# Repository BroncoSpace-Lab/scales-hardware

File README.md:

# scales-hardware
Hardware design files for the Spacecraft Compartmentalized Autonomous Learning and Edge Computing System (SCALES)

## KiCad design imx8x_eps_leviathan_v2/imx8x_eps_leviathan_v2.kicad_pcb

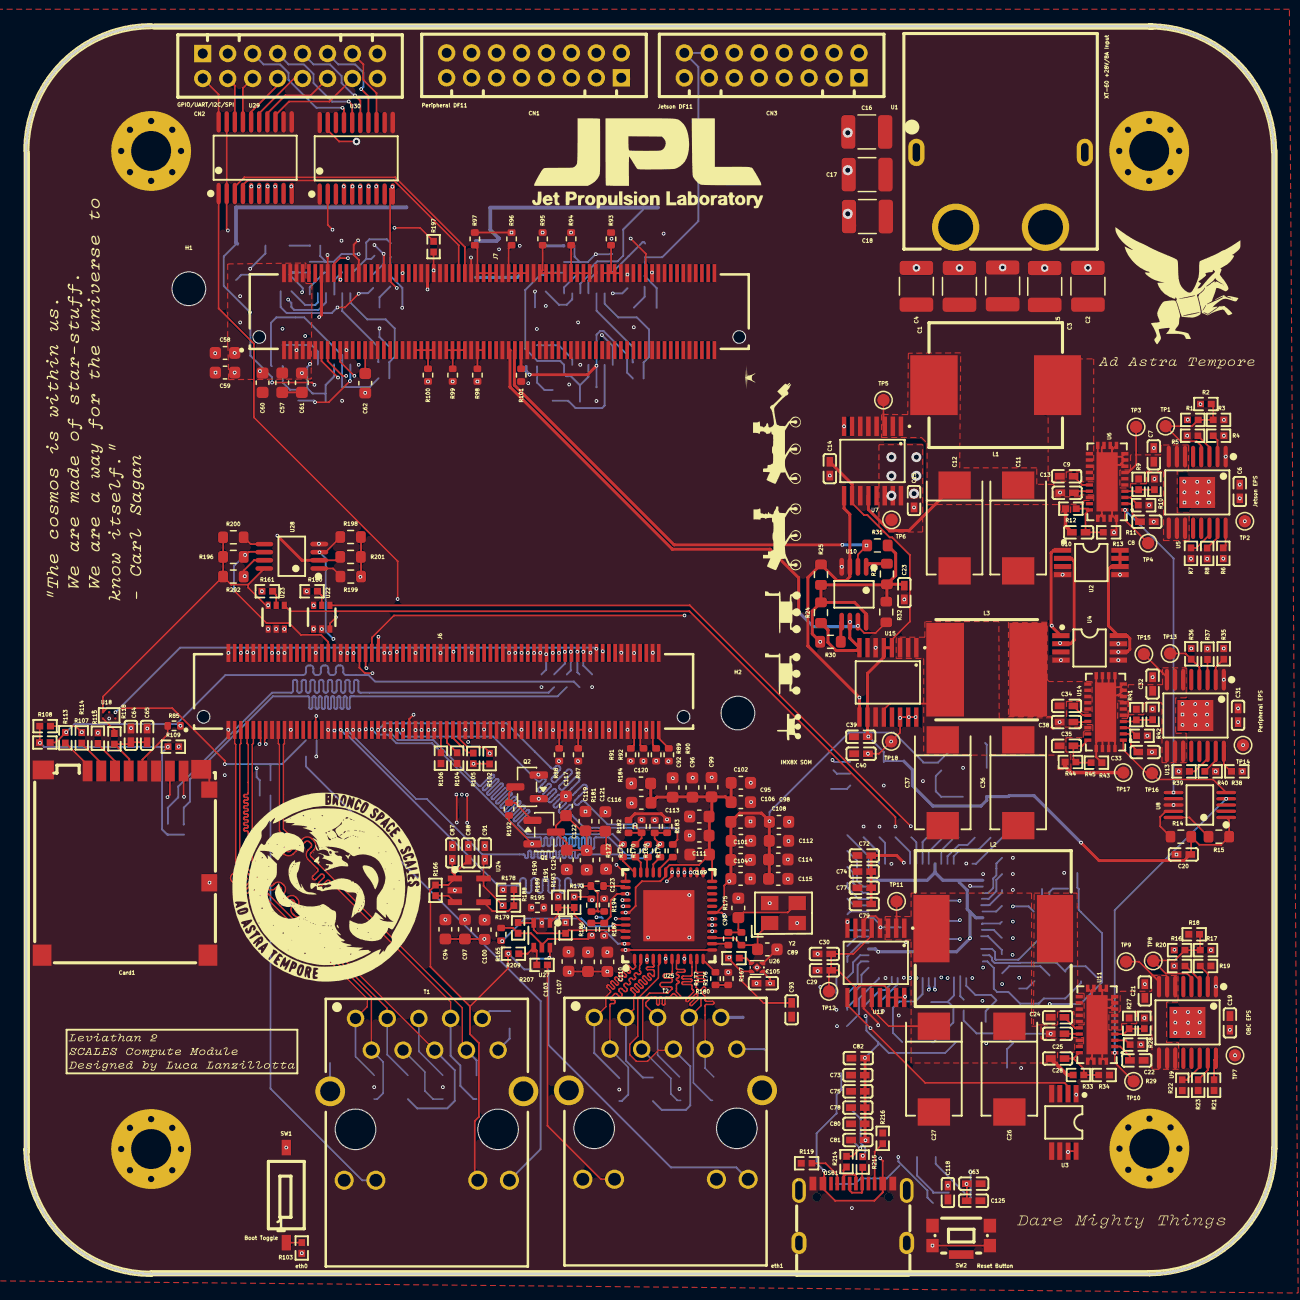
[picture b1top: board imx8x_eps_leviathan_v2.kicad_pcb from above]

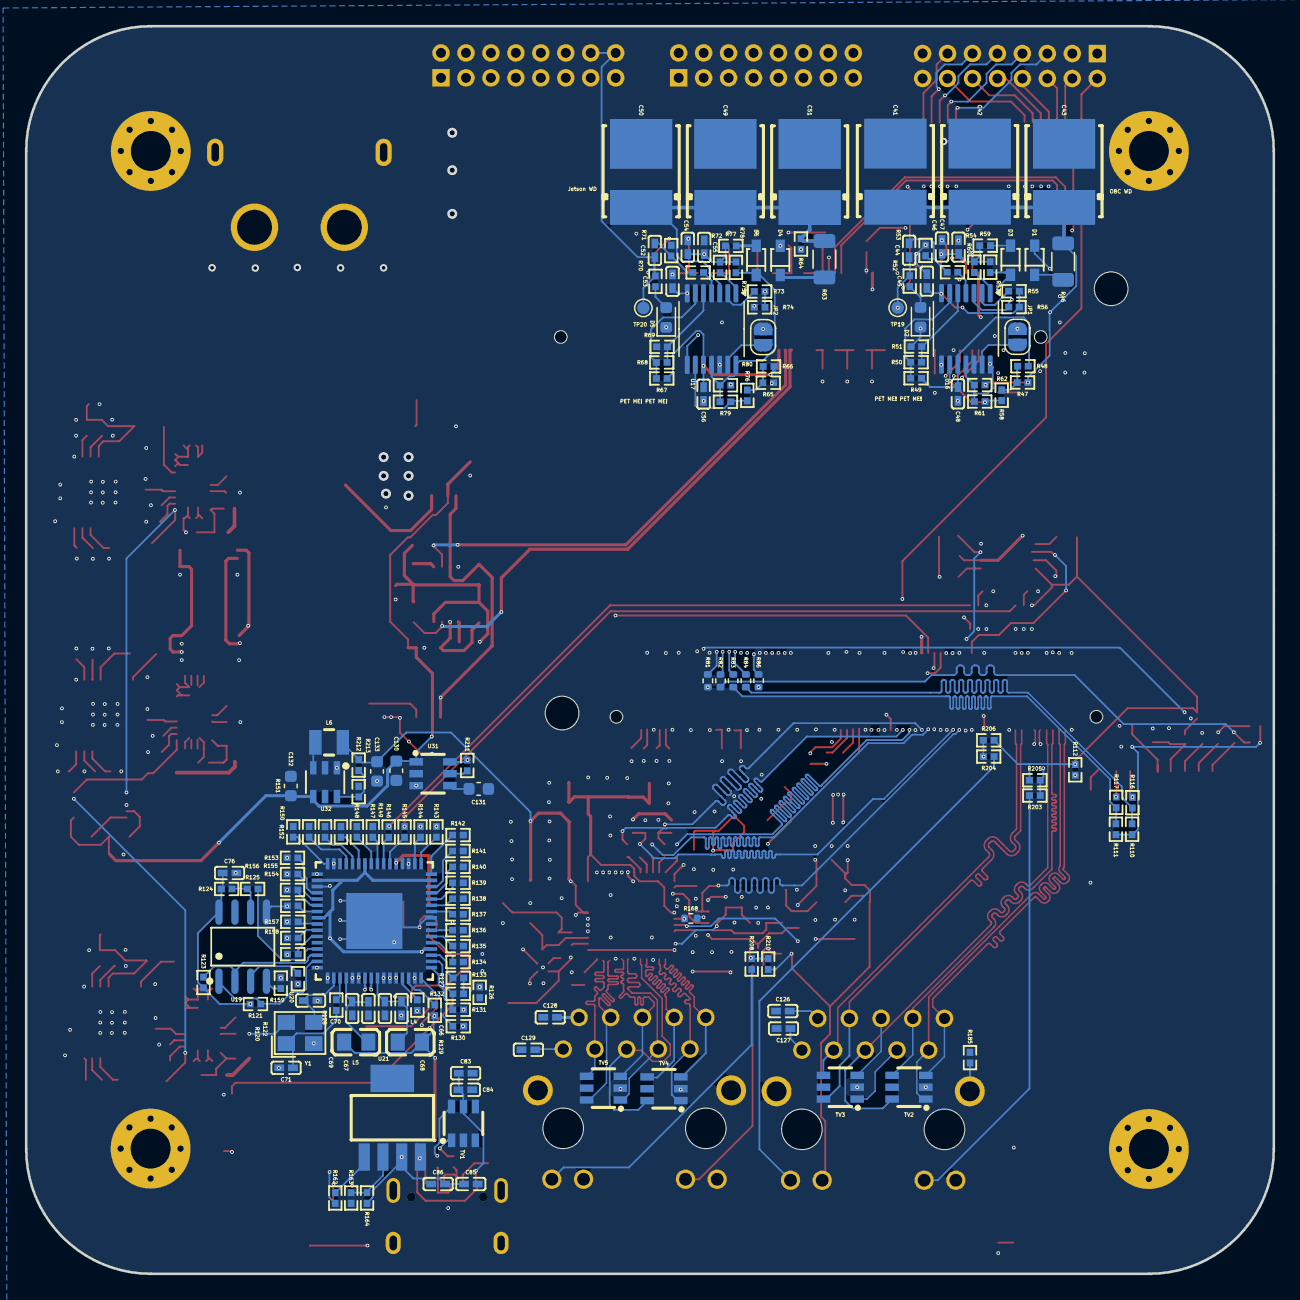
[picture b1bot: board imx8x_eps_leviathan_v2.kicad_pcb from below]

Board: 6 copper layers, 100.0 x 100.0 mm, 441 parts (160 on the bottom side), 317 nets.

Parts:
C1, C2, C3, C4, C5, C16, C17, C18: 10u; C_1210_3225Metric
C6, C19, C31: 220n; C0402
C7, C21, C32: 22n; C0402
C8, C85: 1u; C0402
C9, C13, C14, C15, C20, C23, C24, C28, C29, C30, C34, C38, C39, C40, C63, C68, C69, C74, C75, C76, C77, C78, C79, C80, C82, C84, C86, C87, C88, C91, C93, C105, C125, C126, C127, C128, C129: 100n; C0402
C10, C25, C35: 10p; C0402
C11, C12, C26, C27, C36, C37: 47u; CAP-SMD_L7.3-W4.3-FD
C22, C33: 0.47u; C0402
C41, C42, C43, C49, C50, C51: 100u; CAP-SMD_L7.3-W6.1_TCN4227M025R0100
C44, C45, C46, C47, C48, C52, C53, C54, C55, C56, C64, C65: 10u; C0402
C57, C58: 22u; C_0603_1608Metric
C59, C60, C132: 4.7u; C_0603_1608Metric
C61, C95, C96, C97, C101, C102, C103, C108, C109, C113, C119, C122: 100n; C_0603_1608Metric
C62: 220n; C_0603_1608Metric
C66, C67, C72, C73, C81: 4.7u; C0402
C70, C71: 12p; C0402
C83: 2.2u; C0402
C89, C90: 18p; C_0603_1608Metric
C92, C94, C98, C99, C100, C104, C106, C111, C112, C117, C121, C130: 1u; C_0603_1608Metric
C107, C114, C116, C123: 10n; C_0603_1608Metric
C110, C115, C120, C124, C133: 10u; C_0603_1608Metric
C118: 2.2n; C0402
C131: 47u; C_0603_1608Metric
CN1, CN2, CN3: DF11-16DP-2DSA; CONN-TH_DF11-16DP-2DSA-08
Card1: 5027740891; TF-SMD_5027740891
D1, D3, D4, D6: 1N4448WS-7-F; SOD-323_L1.8-W1.3-LS2.5-RD
D2, D5: GREEN; LED_0603_1608Metric
H1, H2: MountingHole; MountingHole_2.7mm_M2.5
J1, J2, J3, J4: Conn_01x01_Socket; MountingHole_3.2mm_M3_Pad_Via
J6, J7: BTH-070-02-L-D-A; SAMTEC_BTH-070-02-L-D-A
JP1, JP2: SolderJumper_2_Open; SolderJumper-2_P1.3mm_Open_RoundedPad1.0x1.5mm
L1: 35u; IND-SMD_L10.7-W10.0_ETQP5MXXXX
L2: 6.1u; IND-SMD_FTKB1207-6R1NT
L3: 10u; IND-SMD_L8.0-W8.0
L4, L5: 600R/1000MHz; L0805
L6: 2.2u; IND-SMD_L2.5-W2.0_YXMBL252010P
Q1: IRLML6401; SOT-23
Q2: BSS138; SOT-23
R1, R2, R4, R16, R19, R35, R36, R55, R57, R73, R75, R102, R103, R104, R105, R106, R129, R159, R211: 1k; R0402
R3, R5, R6, R7, R8, R20, R21, R22, R23, R37, R38, R39, R40: 15k; R0402
R9, R27, R41: 47k; R0402
R10, R28, R42, R125, R197: 2k; R0402
R11, R29, R43: 110k; R0402
R12: 196k; R0402
R13, R18, R47, R48, R49, R50, R53, R54, R65, R66, R67, R68, R71, R72, R120, R121, R123, R124, R127, R132, R133, R134, R135, R136, R137, R138, R139, R140, R141, R142, R143, R144, R147, R148, R149, R150, R151, R152, R153, R154, R155, R156, R157, R158, R160, R161, R162, R163, R166, R180, R188, R205, R206, R209, R210: 10k; R0402
R14: 14k; R_0603_1608Metric
R15: 17k; R_0603_1608Metric
R17: 56.2k; R0402
R24, R25, R26, R30, R31, R32: 4.7k; R_0603_1608Metric
R33: 240k; R0402
R34, R56, R58, R59, R61, R62, R64, R74, R76, R77, R79, R80, R213: 100k; R0402
R44: 20.8k; R0402
R45: 5k; R0402
R46, R63: 10; R_1206_3216Metric
R51, R52, R69, R70: 3k; R0402
R60, R78: 4.7M; R0402
R81, R82, R83, R84, R85, R86, R169, R170, R171, R172, R173: 22; R_0402_1005Metric
R87, R88, R89, R90, R91, R92, R93, R94, R95, R96, R97, R98, R99, R100, R101, R177, R181, R192, R195: 10k; R_0402_1005Metric
R107, R108, R109, R110, R111, R112: 49.9k; R0402
R113, R114, R115, R116, R117, R130, R131, R145, R146: 22; R0402
R118, R122: 0; R0402
R119, R216: 5.1k; R0402
R126: 12k; R0402
R128, R203, R204, R207, R208: 200; R0402
R164: 16.5k; R0402
R165: 2k; R_0402_1005Metric
R167: 1M; R_0402_1005Metric
R168: 15k; R_0402_1005Metric
R174: 0; R_0402_1005Metric
R175: 100; R_0402_1005Metric
R176: 1k; R_0402_1005Metric
R178: 2.55k; R0402
R179: 13k; R0402
R182, R183, R184, R187, R194: 2.49k; R_0402_1005Metric
R185: 1M; R0402
R186, R193: 5.76k; R_0402_1005Metric
R189, R191: 2.49k; R0402
R190: 5.76k; R0402
R196, R198, R199, R200, R201, R202: 10k; R_0603_1608Metric
R212: 200k; R0402
R214, R215: 27; R0402
SW1: SW_DIP_x01; SW-SMD_1.27-1P-TPPT
SW2: KMR221GLFS; KEY-SMD_KMR2XXGXXX
T1, T2: WE-RJ45_7499111121A; 7499111121A
TP1, TP2, TP3, TP4, TP5, TP6, TP7, TP8, TP9, TP10, TP11, TP12, TP13, TP14, TP15, TP16, TP17, TP18, TP19, TP20: TestPoint; TestPoint_Pad_D1.0mm
TV1, TV2, TV3, TV4, TV5: SRV05-4.TCT; SOT-23-6_L2.9-W1.6-P0.95-LS2.8-BR
U1: XT60PW-F_C428722; TH_2P-XT60PW-F
U2, U3, U4: MCP9808T-E/MS; MSOP-8_L3.0-W3.0-P0.65-LS4.9-BL
U5, U9, U13: TPS1HB08BQPWPRQ1; HTSSOP-16_L5.0-W4.4-P0.65-LS6.4-TL-EP2.9
U6, U11, U14: LT8612EUDE#PBF; QFN-28_L6.0-W3.0-P0.50-BL-EP
U7, U12, U15: INA260AIPWR; TSSOP-16_L5.0-W4.4-P0.65-LS6.4-BL-1
U8: LTC6902; MSOP-10_L3.0-W3.0-P0.50-LS5.0-BL
U10, U28: TCA4307DGKR; VSSOP-8_L3.0-W3.0-P0.65-LS4.9-BL
U16, U17: TLV1704; TSSOP-14_4.4x5mm_P0.65mm
U18: BD2204GUL-E2; BGA-6_L1.5-W1.0-P0.50_BD2204GUL-E2
U19: CAT93C66VI-GT3; SOIC-8_L4.9-W3.9-P1.27-LS6.0-BL
U20: FT2232HL; QFN-64_L9.0-W9.0-P0.50-TL-EP4.3
U21: LP38693MP-ADJ/NOPB; SOT-223-5_L6.5-W3.5-P1.50-LS7.0-BL
U22, U23: TXS0101DCKR; SC-70-6_L2.0-W1.3-P0.65-LS2.1-BR
U24: MCP1824T-ADJE/OT; SOT-23-5_L3.0-W1.7-P0.95-LS2.8-BL
U25: DP83867CRRGZR; VQFN-48_L7.0-W7.0-P0.50-BL-EP4.1
U26: TLV71310PDQNR; X2SON-4_L1.0-W1.0-P0.65-TL-EP
U27: 74LVC2G07GW; SOT-363_L2.1-W1.3-P0.65-LS2.2-BL
U29, U30: TXS0108EPWR; TSSOP-20_L6.5-W4.4-P0.65-LS6.4-BL
U31: TPS22917DBVR; SOT-23-6_L2.9-W1.6-P0.95-LS2.8-BR
U32: TLV62569PDDCR; SOT-23-6_L2.9-W1.6-P0.95-LS2.8-BL
USB1: TYPE-C 16PIN 2MD; USB-C-SMD_TYPE-C-6PIN-2MD-073
Y1: Crystal_GND24; CRYSTAL-SMD_4P-L3.2-W2.5-BL
Y2: 25MHz; CRYSTAL-SMD_4P-L3.2-W2.5-BL-2

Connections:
1V8_FTDI: C72.2, C74.2, C77.2, C79.2, U20.12 (VCORE), U20.37 (VCORE), U20.49 (VREGOUT), U20.64 (VCORE)
3V3_FTDI: C73.2, C75.2, C76.2, C78.2, C80.2, C81.2, C82.2, C85.2, C86.2, L4.1, L5.1, R121.2, R123.2, R124.2, R129.2, R159.1, R164.1, U19.8 (VCC), U20.20 (VCCIO), U20.31 (VCCIO), U20.42 (VCCIO), U20.50 (VREGIN), U20.56 (VCCIO), U21.3 (OUT)
+1.8V_OBC_Perif: C93.1, C95.1, C98.1, C101.1, C104.1, C108.1, C112.1, C114.1, C115.1, C133.1, L6.2, Q1.2 (S), R165.2, R180.1, R181.1, R183.1, R186.1, R188.1, R190.1, R192.1, R193.1, R212.1, U25.19 (VDDIO), U25.30 (VDDIO), U25.41 (VDDIO), U26.4 (IN), U27.5 (VCC)
+3.3V_OBC: C14.1, C20.1, C29.1, C30.1, C39.1, C57.1, C58.1, C59.1, C60.1, C61.1, C130.1, C132.1, D1.2 (A), J7.132 (D66), J7.133 (C67), J7.134 (D67), J7.135 (C68), J7.136 (D68), J7.137 (C69), J7.138 (D69), J7.139 (C70), J7.140 (D70), R14.1, R15.1, R120.2, R197.1, TP12.1 (1_1), U2.6 (A1), U2.7 (A0), U2.8 (VDD), U3.7 (A0), U3.8 (VDD), U4.6 (A1), U4.8 (VDD), U7.10 (VS), U8.1 (V+), U12.5 (A0), U12.10 (VS), U12.14 (IN-), U15.4 (A1), U15.5 (A0), U15.10 (VS), U29.2 (VCCA), U29.19 (VCCB), U30.2 (VCCA), U30.19 (VCCB), U31.1 (VIN), U32.4 (VIN)
+3.3V_OBC_Perif: C23.1, C63.2, C87.1, C88.1, C125.1, R24.1, R25.1, R26.1, R30.1, R31.1, R32.1, R112.2, R166.1, R196.1, R198.1, R199.1, R200.1, R201.1, R202.1, R205.1, R206.1, R209.1, R210.1, R211.1, T1.11, T1.13, T2.11, T2.13, U10.8 (VCC), U18.A1 (VIN1), U22.6 (VCCB), U23.6 (VCCB), U24.1 (VIN), U28.8 (VCC), U31.6 (VOUT)
+5V_Perif: C40.1, CN1.1, CN1.2, CN1.3, CN1.4, CN1.5, CN1.6, CN1.7, CN1.8, TP18.1 (1_1), U15.14 (IN-)
+20V_Jetson: C15.1, C16.1, C17.1, C18.1, CN3.1, CN3.2, CN3.3, CN3.4, CN3.5, CN3.6, CN3.7, CN3.8, D4.2 (A), TP6.1 (1_1), U7.14 (IN-)
+V_Batt: C1.1, C2.1, C3.1, C4.1, C5.1, C6.1, C19.1, C31.1, R17.2, TP2.1 (1_1), TP7.1 (1_1), TP14.1 (1_1), U1.3 (+), U5.17 (VBB), U9.17 (VBB), U13.17 (VBB)
/IMX8XQXP SCALES Mariner Carrier Board/Debug USB - UART/DEBUG_USB_DN: R214.2, TV1.1, U20.7 (DM)
/IMX8XQXP SCALES Mariner Carrier Board/Debug USB - UART/DEBUG_USB_DP: R215.2, TV1.6, U20.8 (DP)
/IMX8XQXP SCALES Mariner Carrier Board/Debug USB - UART/FTDI_OSCI: C70.1, U20.2 (OSCI), Y1.3
/IMX8XQXP SCALES Mariner Carrier Board/Debug USB - UART/FTDI_OSCO: C71.1, R128.2, Y1.1
/IMX8XQXP SCALES Mariner Carrier Board/Debug USB - UART/M40_UART0_RX: R145.1, U23.4 (B)
/IMX8XQXP SCALES Mariner Carrier Board/Debug USB - UART/M40_UART0_TX: R146.1, U22.4 (B)
/SCALES_EPS/Jetson_Subsystem/WD_Jetson/WDT-VIN: R64.2, R65.2, R74.1, R80.1
/SCALES_EPS/Jetson_Subsystem/WD_Jetson/WDT-VP: R68.1, R69.2, U17.5 (+)
/SCALES_EPS/OBC_Subsystem/WD_OBC/WDT-VIN: C41.1, C42.1, C43.1, R46.2, R47.2, R56.1, R62.1, U16.3 (V+)
/SCALES_EPS/OBC_Subsystem/WD_OBC/WDT-VP: R50.1, R51.2, U16.5 (+)
ETH1_A_TX_N: T2.2 (D1-), TV4.1, U25.2 (TD_M_A)
ETH1_A_TX_P: T2.1 (D1+), TV4.3, U25.1 (TD_P_A)
ETH1_B_TX_N: T2.6 (D2-), TV4.6, U25.5 (TD_M_B)
ETH1_B_TX_P: T2.3 (D2+), TV4.4, U25.4 (TD_P_B)
ETH1_C_TXCLK_N: T2.5 (D3-), TV5.3, U25.8 (TD_M_C)
ETH1_C_TXCLK_P: T2.4 (D3+), TV5.1, U25.7 (TD_P_C)
ETH1_D_RXDV_N: T2.8 (D4-), TV5.4, U25.11 (TD_M_D)
ETH1_D_RXDV_P: T2.7 (D4+), TV5.6, U25.10 (TD_P_D)
ETH1_LED0: R208.2, R210.2, U27.6 (1Y)
ETH1_LED2: R207.2, R209.2, U27.4 (2Y)
GND: C1.2, C2.2, C3.2, C4.2, C5.2, C6.2, C7.2, C8.2, C11.2, C12.2, C13.2, C14.2, C15.2, C16.2, C17.2, C18.2, C19.2, C20.2, C21.2, C22.2, C23.2, C26.2, C27.2, C28.2, C29.2, C30.2, C31.2, C32.2, C33.2, C36.2, C37.2, C38.2, C39.2, C40.2, C41.2, C42.2, C43.2, C45.1, C46.1, C47.1, C48.1, C49.2, C50.2, C51.2, C53.1, C54.1, C55.1, C56.1, C57.2, C58.2, C59.2, C60.2, C61.2, C62.2, C63.1, C64.1, C65.1, C66.1, C67.1, C68.1, C69.1, C70.2, C71.2, C72.1, C73.1, C74.1, C75.1, C76.1, C77.1, C78.1, C79.1, C80.1, C81.1, C82.1, C83.1, C84.1, C85.1, C86.1, C87.2, C88.2, C89.1, C90.1, C91.2, C92.2, C93.2, C94.2, C95.2, C96.2, C97.2, C98.2, C99.2, C100.2, C101.2, C102.2, C103.2, C104.2, C105.2, C106.2, C107.2, C108.2, C109.2, C110.2, C111.2, C112.2, C113.2, C114.2, C115.2, C116.2, C117.2, C118.2, C119.2, C120.2, C121.2, C122.2, C123.2, C124.2, C125.2, C126.2, C127.2, C128.2, C129.2, C130.2, C131.2, C132.2, C133.2, CN1.9, CN1.10, CN1.12, CN1.14, CN1.16, CN2.15, CN2.16, CN3.9, CN3.10, CN3.11, CN3.12, CN3.13, CN3.15, Card1.6 (VSS), Card1.10 (DET), Card1.11 (SHELL), Card1.12 (SHELL), Card1.13 (SHELL), Card1.14 (SHELL), D2.1 (K), D5.1 (K), J1.1 (1_1), J2.1 (1_1), J3.1 (1_1), J4.1 (1_1), J6.03 (A2), J6.06 (B3), J6.09 (A5), J6.12 (B6), J6.13 (A7), J6.18 (B9), J6.23 (A12), J6.24 (B12), J6.30 (B15), J6.36 (B18), J6.39 (A20), J6.40 (B20), J6.46 (B23), J6.49 (A25), J6.52 (B26), J6.58 (B29), J6.61 (A31), J6.64 (B32), J6.71 (A36), J6.74 (B37), J6.79 (A40), J6.80 (B40), J6.89 (A45), J6.90 (B45), J6.100 (B50), J6.103 (A52), J6.108 (B54), J6.111 (A56), J6.120 (B60), J6.121 (A61), J6.126 (B63), J6.131 (A66), J6.139 (A70), J6.140 (B70), J7.09 (C5), J7.10 (D5), J7.19 (C10), J7.22 (D11), J7.29 (C15), J7.36 (D18), J7.39 (C20), J7.46 (D23), J7.49 (C25), J7.56 (D28), J7.59 (C30), J7.62 (D31), J7.69 (C35), J7.70 (D35), J7.79 (C40), J7.80 (D40), J7.89 (C45), J7.90 (D45), J7.95 (C48), J7.100 (D50), J7.107 (C54), J7.112 (D56), J7.115 (C58), J7.120 (D60), J7.125 (C63), J7.130 (D65), Q2.2 (S), R3.2, R4.1, R5.2, R6.2, R7.2, R8.2, R10.2, R11.2, R13.2, R18.1, R19.1, R20.1, R21.2, R22.2, R23.2, R28.2, R29.2, R34.2, R35.1, R37.1, R38.1, R39.1, R40.1, R42.2, R43.2, R45.2, R51.1, R53.1, R69.1, R71.1, R87.1, R88.1, R89.1, R90.1, R91.1, R92.1, R93.1, R94.1, R95.1, R96.1, R97.1, R98.1, R99.1, R100.1, R101.1, R103.1, R104.1, R106.1, R119.2, R122.1, R126.1, R127.1, R132.1, R133.1, R134.1, R135.1, R136.1, R137.1, R138.1, R139.1, R140.1, R141.1, R142.1, R143.1, R144.1, R147.1, R148.1, R149.1, R150.1, R151.1, R152.1, R153.1, R154.1, R155.1, R156.1, R157.1, R158.1, R163.1, R177.2, R178.1, R182.2, R184.2, R185.1, R187.2, R189.2, R191.2, R194.2, R195.2, R213.2, R216.2, SW2.3, SW2.4, TV1.2, TV2.2, TV3.2, TV4.2, TV5.2, U1.1, U1.2, U1.4 (-), U2.4 (GND), U2.5 (A2), U3.4 (GND), U3.5 (A2), U3.6 (A1), U4.4 (GND), U4.5 (A2), U4.7 (A0), U5.1 (GND), U6.8 (PGND), U6.11 (GND), U6.25 (NC), U7.4 (A1), U7.5 (A0), U7.6 (GND), U8.8 (GND), U9.1 (GND), U10.4 (GND), U11.8 (PGND), U11.11 (GND), U11.25 (NC), U12.4 (A1), U12.6 (GND), U13.1 (GND), U14.8 (PGND), U14.11 (GND), U14.25 (NC), U15.6 (GND), U16.12 (V-), U17.12 (V-), U18.B2 (GND), U19.5 (GND), U20.1 (GND), U20.5 (GND), U20.10 (AGND), U20.11 (GND), U20.15 (GND), U20.25 (GND), U20.35 (GND), U20.47 (GND), U20.51 (GND), U20.65 (GND), U21.5 (GND), U22.2 (GND), U23.2 (GND), U24.2 (GND), U25.49 (GND), U26.2 (GND), U26.5 (PAD), U27.2 (GND), U28.4 (GND), U29.11 (GND), U30.11 (GND), U31.2 (GND), U32.2 (GND), USB1.1 (GND), USB1.12 (GND), USB1.13 (SHELL), USB1.14 (SHELL), Y1.2 (G), Y1.4 (G), Y2.2 (G), Y2.4 (G)
GNDPWR: C118.1, R185.2, T1.S1 (SHIELD1), T1.S2 (SHIELD2), T2.S1 (SHIELD1), T2.S2 (SHIELD2)
I2C3_USR_SCL: CN2.3, R201.2, U28.2 (SCLOUT)
I2C3_USR_SDA: CN2.1, R202.2, U28.7 (SDAOUT)
LED0_LINK: R190.2, R191.1, U25.47 (LED_0), U27.1 (1A)
LED2_ACT: R188.2, R189.1, U25.45 (LED_2), U27.3 (2A)
unnamed: C44.2, R53.2, R54.2
unnamed: C52.2, R71.2, R72.2
unnamed: C90.2, R167.2, R175.1, Y2.3
unnamed: Card1.2 (CD/DAT3), R114.1
unnamed: Card1.3 (CMD), R115.1
unnamed: Card1.7 (DAT0), R116.1
unnamed: Card1.8 (DAT1), R117.1
unnamed: Card1.1 (DAT2), R113.1
unnamed: C64.2, C65.2, Card1.4 (VDD), R118.1
unnamed: D1.1 (C), R46.1
unnamed: D2.2 (A), R52.1
unnamed: D3.2 (A), R59.2
unnamed: D3.1 (C), R60.2, R61.2, R62.2, U16.11 (+), U16.14
unnamed: D4.1 (C), R63.1
unnamed: D5.2 (A), R70.1
unnamed: D6.2 (A), R77.2
unnamed: D6.1 (C), R78.2, R79.2, R80.2, U17.11 (+), U17.14
unnamed: J6.25 (A13), R81.2
unnamed: J6.27 (A14), R82.2
unnamed: J6.29 (A15), R83.2
unnamed: J6.31 (A16), R84.2
unnamed: J6.35 (A18), R85.2
unnamed: J6.37 (A19), R86.2
unnamed: J6.02 (B1), R89.2
unnamed: J6.04 (B2), R90.2
unnamed: J6.08 (B4), R91.2
unnamed: J6.10 (B5), R92.2
unnamed: J6.26 (B13), J6.28 (B14), R87.2
unnamed: J6.32 (B16), J6.34 (B17), R88.2
unnamed: J7.31 (C16), J7.33 (C17), J7.35 (C18), J7.37 (C19), R93.2
unnamed: J7.41 (C21), J7.43 (C22), J7.45 (C23), J7.47 (C24), R94.2
unnamed: J7.51 (C26), J7.53 (C27), J7.55 (C28), J7.57 (C29), R95.2
unnamed: J7.61 (C31), J7.63 (C32), J7.65 (C33), J7.67 (C34), R96.2
unnamed: J7.71 (C36), J7.73 (C37), J7.75 (C38), J7.77 (C39), R97.2
unnamed: J7.64 (D32), R101.2
unnamed: J7.76 (D38), J7.78 (D39), R98.2
unnamed: J7.82 (D41), J7.84 (D42), J7.86 (D43), J7.88 (D44), R99.2
unnamed: J7.92 (D46), J7.94 (D47), J7.96 (D48), J7.98 (D49), R100.2
unnamed: JP1.1 (A), U16.13
unnamed: JP2.1 (A), U17.13
unnamed: C117.1, C119.1, C121.1, C122.1, C123.1, C124.1, Q1.3 (D), U25.13 (VDDA1P8), U25.48 (VDDA1P8)
unnamed: Q1.1 (G), Q2.3 (D), R192.2
unnamed: R8.1, U5.15 (NC)
unnamed: R23.1, U9.15 (NC)
unnamed: R40.2, U13.15 (NC)
unnamed: R47.1, R48.2, R58.1
unnamed: R55.2, U16.2
unnamed: R57.2, U16.1
unnamed: R65.1, R66.2, R76.1
unnamed: R73.2, U17.2
unnamed: R75.2, U17.1
unnamed: R103.2, SW1.1
unnamed: R176.2, R177.1
unnamed: R203.1, T1.12
unnamed: R204.1, T1.14
unnamed: R207.1, T2.12
unnamed: R208.1, T2.14
unnamed: C127.1, T1.10 (GND)
unnamed: C126.1, T1.9 (VCC)
unnamed: C129.1, T2.10 (GND)
unnamed: C128.1, T2.9 (VCC)
unnamed: R6.1, U5.16 (DIA_EN)
unnamed: R1.1, R2.2, R3.1, TP1.1 (1_1), U5.4 (EN)
unnamed: R5.1, U5.3 (LATCH)
unnamed: R7.1, U5.14 (SEL1)
unnamed: R4.2, U5.2 (SNS)
unnamed: C7.1, R9.1, TP3.1 (1_1), U5.6 (VOUT), U6.5 (VIN)
unnamed: C10.1, C11.1, C12.1, L1.2, R12.1, TP5.1 (1_1), U6.22 (BIAS), U7.1 (IN+), U7.12 (VBUS)
unnamed: C9.1, U6.20 (BST)
unnamed: R9.2, R10.1, U6.4 (EN/UV)
unnamed: C10.2, R12.2, R13.1, U6.24 (FB)
unnamed: C13.1, U6.21 (INTVCC)
unnamed: R11.1, U6.3 (RT)
unnamed: C9.2, L1.1, U6.15 (SW)
unnamed: C8.1, U6.2 (TR/SS)
unnamed: R14.2, U8.9 (MOD)
unnamed: R15.2, U8.10 (SET)
unnamed: R21.1, U9.16 (DIA_EN)
unnamed: R16.1, R17.1, R18.2, TP8.1 (1_1), U9.4 (EN)
unnamed: R20.2, U9.3 (LATCH)
unnamed: R22.1, U9.14 (SEL1)
unnamed: R19.2, U9.2 (SNS)
unnamed: R26.2, U10.1 (EN)
unnamed: R30.2, U10.5 (READY)
unnamed: C25.1, C26.1, C27.1, L2.2, R33.1, TP11.1 (1_1), U11.22 (BIAS), U12.1 (IN+), U12.12 (VBUS)
unnamed: C24.1, U11.20 (BST)
unnamed: R27.2, R28.1, U11.4 (EN/UV)
unnamed: C25.2, R33.2, R34.1, U11.24 (FB)
unnamed: C28.1, U11.21 (INTVCC)
unnamed: R29.1, U11.3 (RT)
unnamed: C24.2, L2.1, U11.15 (SW)
unnamed: C22.1, U11.2 (TR/SS)
unnamed: C21.1, R27.1, TP9.1 (1_1), U9.6 (VOUT), U11.5 (VIN)
unnamed: R38.2, U13.16 (DIA_EN)
unnamed: R36.1, TP13.1 (1_1), U13.4 (EN)
unnamed: R37.2, U13.3 (LATCH)
unnamed: R39.2, U13.14 (SEL1)
unnamed: R35.2, U13.2 (SNS)
unnamed: C32.1, R41.1, TP15.1 (1_1), U13.6 (VOUT), U14.5 (VIN)
unnamed: C35.1, C36.1, C37.1, L3.2, R44.1, TP17.1 (1_1), U14.22 (BIAS), U15.1 (IN+), U15.12 (VBUS)
unnamed: C34.1, U14.20 (BST)
unnamed: R41.2, R42.1, U14.4 (EN/UV)
unnamed: C35.2, R44.2, R45.1, U14.24 (FB)
unnamed: C38.1, U14.21 (INTVCC)
unnamed: R43.1, U14.3 (RT)
unnamed: C34.2, L3.1, U14.15 (SW)
unnamed: C33.1, U14.2 (TR/SS)
unnamed: R54.1, U16.4 (-)
unnamed: C45.2, R55.1, R56.2, U16.7 (+)
unnamed: R49.1, R50.2, U16.6 (-)
unnamed: R58.2, R61.1, U16.9 (+)
unnamed: C46.2, C47.2, R57.1, R59.1, R60.1, U16.8 (-)
unnamed: C48.2, R48.1, R49.2, U16.10 (-)
unnamed: R72.1, U17.4 (-)
unnamed: C53.2, R73.1, R74.2, U17.7 (+)
unnamed: R67.1, R68.2, U17.6 (-)
unnamed: R76.2, R79.1, U17.9 (+)
unnamed: C54.2, C55.2, R75.1, R77.1, R78.1, U17.8 (-)
unnamed: C56.2, R66.1, R67.2, U17.10 (-)
unnamed: C49.1, C50.1, C51.1, R63.2, R64.1, U17.3 (V+)
unnamed: R121.1, U19.1 (CS), U20.63 (EECS)
unnamed: R120.1, U19.3 (DI)
unnamed: R122.2, U19.4 (DO)
unnamed: R124.1, R125.2, U19.6 (ORG)
unnamed: R123.1, U19.2 (SK), U20.62 (EECLK)
unnamed: R137.2, U20.26 (ACBUS0)
unnamed: R138.2, U20.27 (ACBUS1)
unnamed: R139.2, U20.28 (ACBUS2)
unnamed: R140.2, U20.29 (ACBUS3)
unnamed: R141.2, U20.30 (ACBUS4)
unnamed: R142.2, U20.32 (ACBUS5)
unnamed: R143.2, U20.33 (ACBUS6)
unnamed: R144.2, U20.34 (ACBUS7)
unnamed: R130.2, U20.16 (ADBUS0)
unnamed: R131.2, U20.17 (ADBUS1)
unnamed: R132.2, U20.18 (ADBUS2)
unnamed: R133.2, U20.19 (ADBUS3)
unnamed: R134.2, U20.21 (ADBUS4)
unnamed: R135.2, U20.22 (ADBUS5)
unnamed: R136.2, U20.23 (ADBUS6)
unnamed: R152.2, U20.48 (BCBUS0)
unnamed: R153.2, U20.52 (BCBUS1)
unnamed: R154.2, U20.53 (BCBUS2)
unnamed: R155.2, U20.54 (BCBUS3)
unnamed: R156.2, U20.55 (BCBUS4)
unnamed: R157.2, U20.57 (BCBUS5)
unnamed: R158.2, U20.58 (BCBUS6)
unnamed: R159.2, U20.59 (BCBUS7)
unnamed: R145.2, U20.38 (BDBUS0)
unnamed: R146.2, U20.39 (BDBUS1)
unnamed: R147.2, U20.40 (BDBUS2)
unnamed: R148.2, U20.41 (BDBUS3)
unnamed: R149.2, U20.43 (BDBUS4)
unnamed: R150.2, U20.44 (BDBUS5)
unnamed: R151.2, U20.45 (BDBUS6)
unnamed: R125.1, U20.61 (EEDATA)
unnamed: R128.1, U20.3 (OSCO)
unnamed: R126.2, U20.6 (REF)
unnamed: R127.2, U20.13 (TEST)
unnamed: C67.2, C69.2, L5.2, U20.4 (VPHY)
unnamed: C66.2, C68.2, L4.2, U20.9 (VPLL)
unnamed: R129.1, U20.14 (~RESET)
unnamed: R163.2, R164.2, U21.2 (ADJ)
unnamed: R162.1, U21.1 (EN)
unnamed: R160.1, U22.5 (OE)
unnamed: R161.1, U23.5 (OE)
unnamed: R178.2, R179.1, U24.4 (ADJ)
unnamed: R166.2, U24.3 (EN)
unnamed: R176.1, U25.12 (RBIAS)
unnamed: R168.1, U25.43 (RESET_N)
unnamed: R174.1, U25.32 (RX_CLK)
unnamed: R173.1, U25.38 (RX_CTRL)
unnamed: R169.1, U25.33 (RX_D0)
unnamed: R170.1, U25.34 (RX_D1)
unnamed: R171.1, U25.35 (RX_D2)
unnamed: R172.1, U25.36 (RX_D3)
unnamed: C89.2, R167.1, U25.15 (X_I), Y2.1
unnamed: R175.2, U25.14 (X_O)
unnamed: R180.2, U26.3 (EN)
unnamed: R199.2, U28.1 (EN)
unnamed: R200.2, U28.5 (READY)
unnamed: CN2.2, U29.20 (B1)
unnamed: CN2.4, U29.18 (B2)
unnamed: CN2.6, U29.17 (B3)
unnamed: CN2.8, U29.16 (B4)
unnamed: CN2.10, U29.15 (B5)
unnamed: CN2.12, U29.14 (B6)
unnamed: CN2.14, U29.13 (B7)
unnamed: CN2.5, U30.17 (B3)
unnamed: CN2.7, U30.16 (B4)
unnamed: CN2.9, U30.15 (B5)
unnamed: CN2.11, U30.14 (B6)
unnamed: CN2.13, U30.13 (B7)
unnamed: C131.1, U31.4 (CT)
unnamed: R211.2, U31.5 (QOD)
unnamed: R212.2, R213.1, U32.6 (FB)
unnamed: L6.1, U32.3 (SW)
unnamed: R119.1, USB1.4 (CC1)
unnamed: R216.1, USB1.10 (CC2)
unnamed: R214.1, USB1.5 (DN2), USB1.7 (DN1)
unnamed: R215.1, USB1.6 (DP1), USB1.8 (DP2)
SCL: R25.2, U2.2 (SCL), U3.2 (SCL), U4.2 (SCL), U7.9 (SCL), U10.3 (SCLIN), U12.9 (SCL), U15.9 (SCL)
SD1_SPWR: R118.2, U18.B1 (VOUT)
SDA: R24.2, U2.1 (SDA), U3.1 (SDA), U4.1 (SDA), U7.8 (SDA), U10.6 (SDAIN), U12.8 (SDA), U15.8 (SDA)
SYNC_PHASE1: TP10.1 (1_1), U8.4 (OUT1), U11.1 (SYNC)
SYNC_PHASE2: TP16.1 (1_1), U8.5 (OUT2), U14.1 (SYNC)
SYNC_PHASE3: TP4.1 (1_1), U6.1 (SYNC), U8.6 (OUT3)
VBUS_DEBUG_USB: C83.2, C84.2, TV1.5, U21.4 (IN), USB1.2 (VBUS), USB1.11 (VBUS)
VCC_1V8_OUT: J7.127 (C64), R160.2, R161.2, U22.1 (VCCA), U23.1 (VCCA)
VCC_ENET_2V5: C91.1, C94.1, C97.1, C100.1, C103.1, C107.1, C110.1, Q2.1 (G), R179.2, R195.1, U24.5 (OUT), U25.3 (VDDA2P5), U25.9 (VDDA2P5)
VCC_LDO_SD1: J6.33 (A17), R107.2, R108.2, R109.2, R110.2, R111.2
VCC_SCU_1V8: J7.93 (C47), R102.2, R105.2
VDD_ADC_1V8: C62.1, J7.114 (D57)
VDD_ETH_1V0: C92.1, C96.1, C99.1, C102.1, C105.1, C106.1, C109.1, C111.1, C113.1, C116.1, C120.1, U25.6 (VDD1P0), U25.24 (VDD1P0), U25.31 (VDD1P0), U25.42 (VDD1P0), U26.1 (OUT)
WD_JETSON: C52.1, CN3.14, CN3.16, R70.2, TP20.1 (1_1)
X_ADMA_I2C0_SCL: J7.66 (D33), R31.2, U10.2 (SCLOUT)
X_ADMA_I2C0_SDA: J7.68 (D34), R32.2, U10.7 (SDAOUT)
X_ADMA_I2C3_SCL: J6.112 (B56), R198.2, U28.3 (SCLIN)
X_ADMA_I2C3_SDA: J6.107 (A54), R196.2, U28.6 (SDAIN)
X_ADMA_SPI2_CS0: J6.41 (A21), U30.5 (A4)
X_ADMA_SPI2_CS1: J6.67 (A34), U30.4 (A3)
X_ADMA_SPI2_SCK: J6.43 (A22), U30.6 (A5)
X_ADMA_SPI2_SDI: J6.45 (A23), U30.7 (A6)
X_ADMA_SPI2_SDO: J6.47 (A24), U30.8 (A7)
X_ADMA_UART0_RX: J6.97 (A49), R130.1
X_ADMA_UART0_TX: J6.95 (A48), R131.1
X_ADMA_UART2_RX: J6.99 (A50), U29.7 (A6)
X_ADMA_UART2_TX: J6.101 (A51), U29.8 (A7)
X_BOOT_MODE0: J6.66 (B33), R102.1, SW1.2
X_BOOT_MODE1: J6.68 (B34), R105.1
X_BOOT_MODE2: J6.70 (B35), R104.2
X_BOOT_MODE3: J6.72 (B36), R106.2
X_CONN_ENET1_REFCLK: J6.106 (B53), U25.18 (CLK_OUT)
X_CONN_ENET1_RXC: J6.86 (B43), R174.2
X_CONN_ENET1_RXD0: J6.102 (B51), R169.2, R183.2, R184.1
X_CONN_ENET1_RXD1: J6.94 (B47), R170.2
X_CONN_ENET1_RXD2: J6.92 (B46), R171.2, R181.2, R182.1
X_CONN_ENET1_RXD3: J6.88 (B44), R172.2
X_CONN_ENET1_RX_CTL: J6.104 (B52), R173.2, R193.2, R194.1
X_CONN_ENET1_TXC: J6.78 (B39), U25.29 (GTX_CLK)
X_CONN_ENET1_TXD0: J6.96 (B48), U25.28 (TX_D0)
X_CONN_ENET1_TXD1: J6.98 (B49), U25.27 (TX_D1)
X_CONN_ENET1_TXD2: J6.76 (B38), U25.26 (TX_D2)
X_CONN_ENET1_TXD3: J6.82 (B41), U25.25 (TX_D3)
X_CONN_ENET1_TX_CTL: J6.84 (B42), U25.37 (TX_CTRL)
X_CONN_ETH0_MDC: J6.135 (A68), U25.16 (MDC)
X_CONN_ETH0_MDIO: J6.133 (A67), U25.17 (MDIO)
X_CONN_USDHC1_CD_B: Card1.9 (SW), J6.19 (A10), R112.1
X_CONN_USDHC1_CLK: Card1.5 (CLK), R85.1
X_CONN_USDHC1_CMD: R86.1, R109.1, R115.2
X_CONN_USDHC1_DATA0: R84.1, R110.1, R116.2
X_CONN_USDHC1_DATA1: R83.1, R111.1, R117.2
X_CONN_USDHC1_DATA2: R82.1, R107.1, R113.2
X_CONN_USDHC1_DATA3: R81.1, R108.1, R114.2
X_CONN_USDHC1_RESET_B: J6.21 (A11), U18.A3 (EN)
X_ETH0_A_TX_N: J6.136 (B68), T1.2 (D1-), TV2.1
X_ETH0_A_TX_P: J6.138 (B69), T1.1 (D1+), TV2.3
X_ETH0_B_TX_N: J6.132 (B66), T1.6 (D2-), TV2.6
X_ETH0_B_TX_P: J6.134 (B67), T1.3 (D2+), TV2.4
X_ETH0_C_TXCLK_N: J6.128 (B64), T1.5 (D3-), TV3.3
X_ETH0_C_TXCLK_P: J6.130 (B65), T1.4 (D3+), TV3.1
X_ETH0_D_RXDV_N: J6.122 (B61), T1.8 (D4-), TV3.4
X_ETH0_D_RXDV_P: J6.124 (B62), T1.7 (D4+), TV3.6
X_ETH0_LED0: J6.123 (A62), R204.2, R206.2
X_ETH0_LED1: J6.125 (A63), R203.2, R205.2
X_ETH1_GPIO0: J7.122 (D61), R186.2, R187.1, U25.39 (GPIO_0)
X_ETH1_GPIO1: J7.128 (D64), U25.40 (GPIO_1)
X_ETH1_PHY_INT: J7.126 (D63), R165.1, U25.44 (INT/PWDN)
X_LSIO_GPIO1_IO17: J6.85 (A43), U29.1 (A1)
X_LSIO_GPIO1_IO18: J6.87 (A44), R36.2
X_LSIO_GPIO1_IO19: J6.93 (A47), R2.1
X_LSIO_GPIO1_IO20: C44.1, J6.91 (A46), R52.2, TP19.1 (1_1)
X_LSIO_GPIO1_IO25: J7.23 (C12), U29.6 (A5)
X_LSIO_GPIO1_IO26: J7.21 (C11), U29.5 (A4)
X_LSIO_GPIO1_IO29: J7.81 (C41), U29.3 (A2)
X_LSIO_GPIO1_IO30: J7.83 (C42), U29.4 (A3)
X_M40_UART0_RX: J7.121 (C61), U23.3 (A)
X_M40_UART0_TX: J7.123 (C62), U22.3 (A)
X_PGOOD: J7.105 (C53), R162.2, U29.10 (OE), U30.10 (OE), U31.3 (ON), U32.1 (EN)
X_POR_B_1V8: J7.101 (C51), R168.2
~WD_EN_JETSON: JP2.2 (B), R1.2
~WD_EN_OBC: JP1.2 (B), R16.2
~X_nRESET_IN: J7.91 (C46), R197.2, SW2.1, SW2.2

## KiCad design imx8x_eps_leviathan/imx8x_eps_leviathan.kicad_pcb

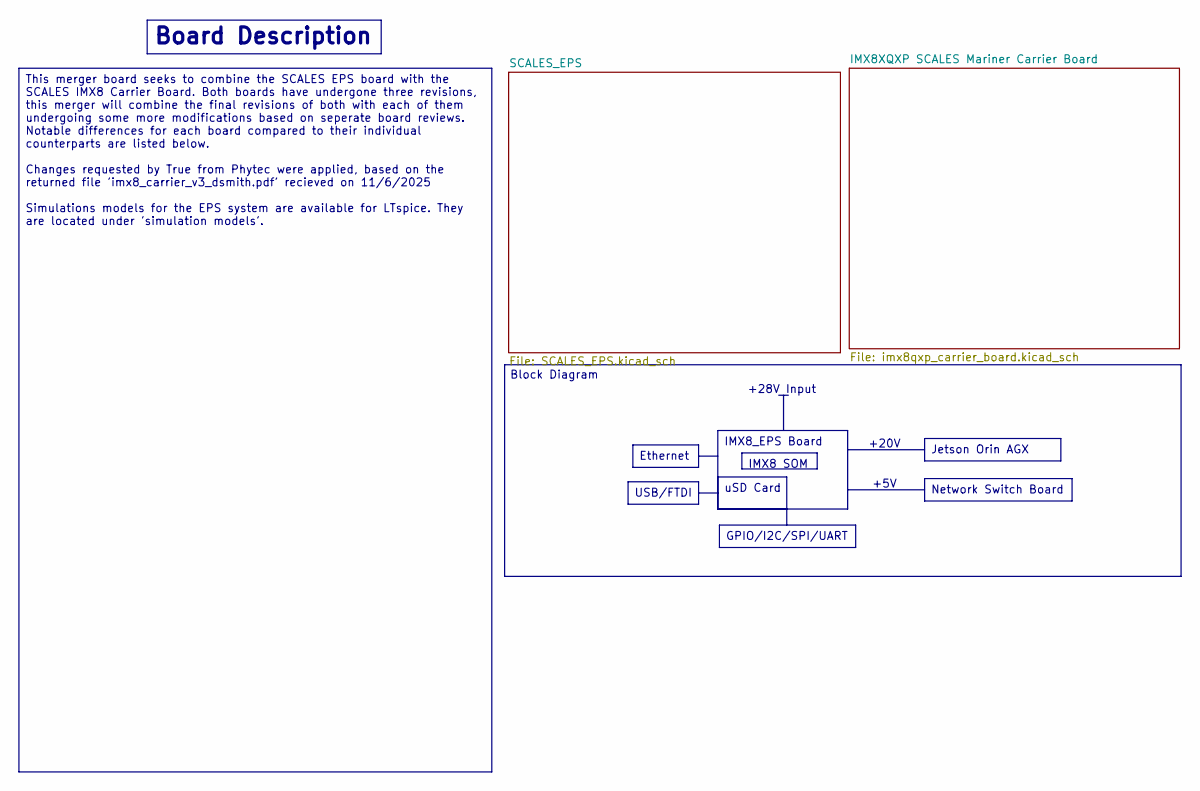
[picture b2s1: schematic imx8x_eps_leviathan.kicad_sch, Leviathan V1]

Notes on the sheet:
Block Diagram
+20V
+28V Input
+5V
USB/FTDI
IMX8 SOM
GPIO/I2C/SPI/UART
Board Description
IMX8_EPS Board
Jetson Orin AGX
uSD Card
Ethernet
This merger board seeks to combine the SCALES EPS board with the SCALES IMX8 Carrier Board. Both boards have undergone three revisions, this merger will combine the final revisions of both with each of them undergoing some more modifications based on seperate board reviews. Notable differences for 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
Network Switch Board

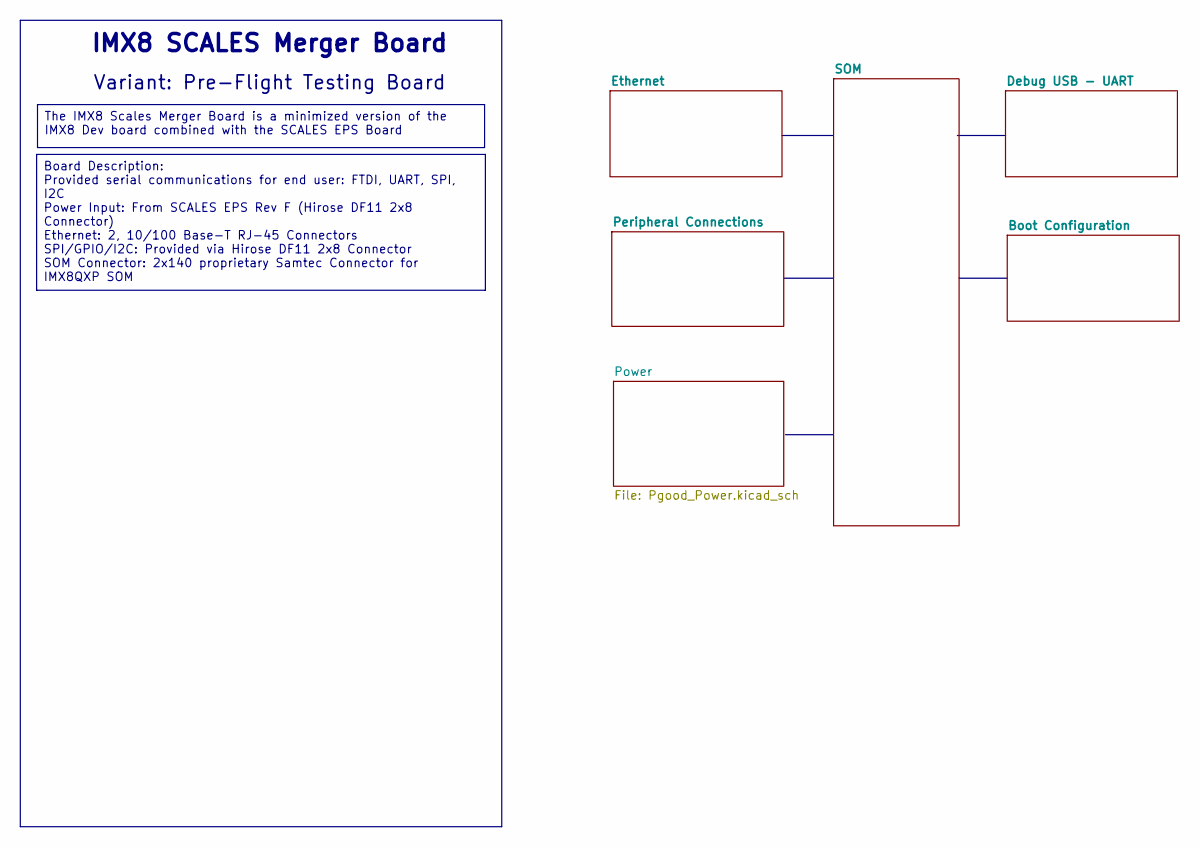
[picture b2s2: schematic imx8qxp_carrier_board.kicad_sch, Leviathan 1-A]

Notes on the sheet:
Variant: Pre-Flight Testing Board
IMX8 SCALES Merger Board
The IMX8 Scales Merger Board is a minimized version of the IMX8 Dev board combined with the SCALES EPS Board
Board Description: Provided serial communications for end user: FTDI, UART, SPI, I2C Power Input: From SCALES EPS Rev F (Hirose DF11 2x8 Connector) Ethernet: 2, 10/100 Base-T RJ-45 Connectors SPI/GPIO/I2C: Provided via Hirose DF11 2x8 Connector SOM Connector: 2x140 proprietary Samtec Connector for 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

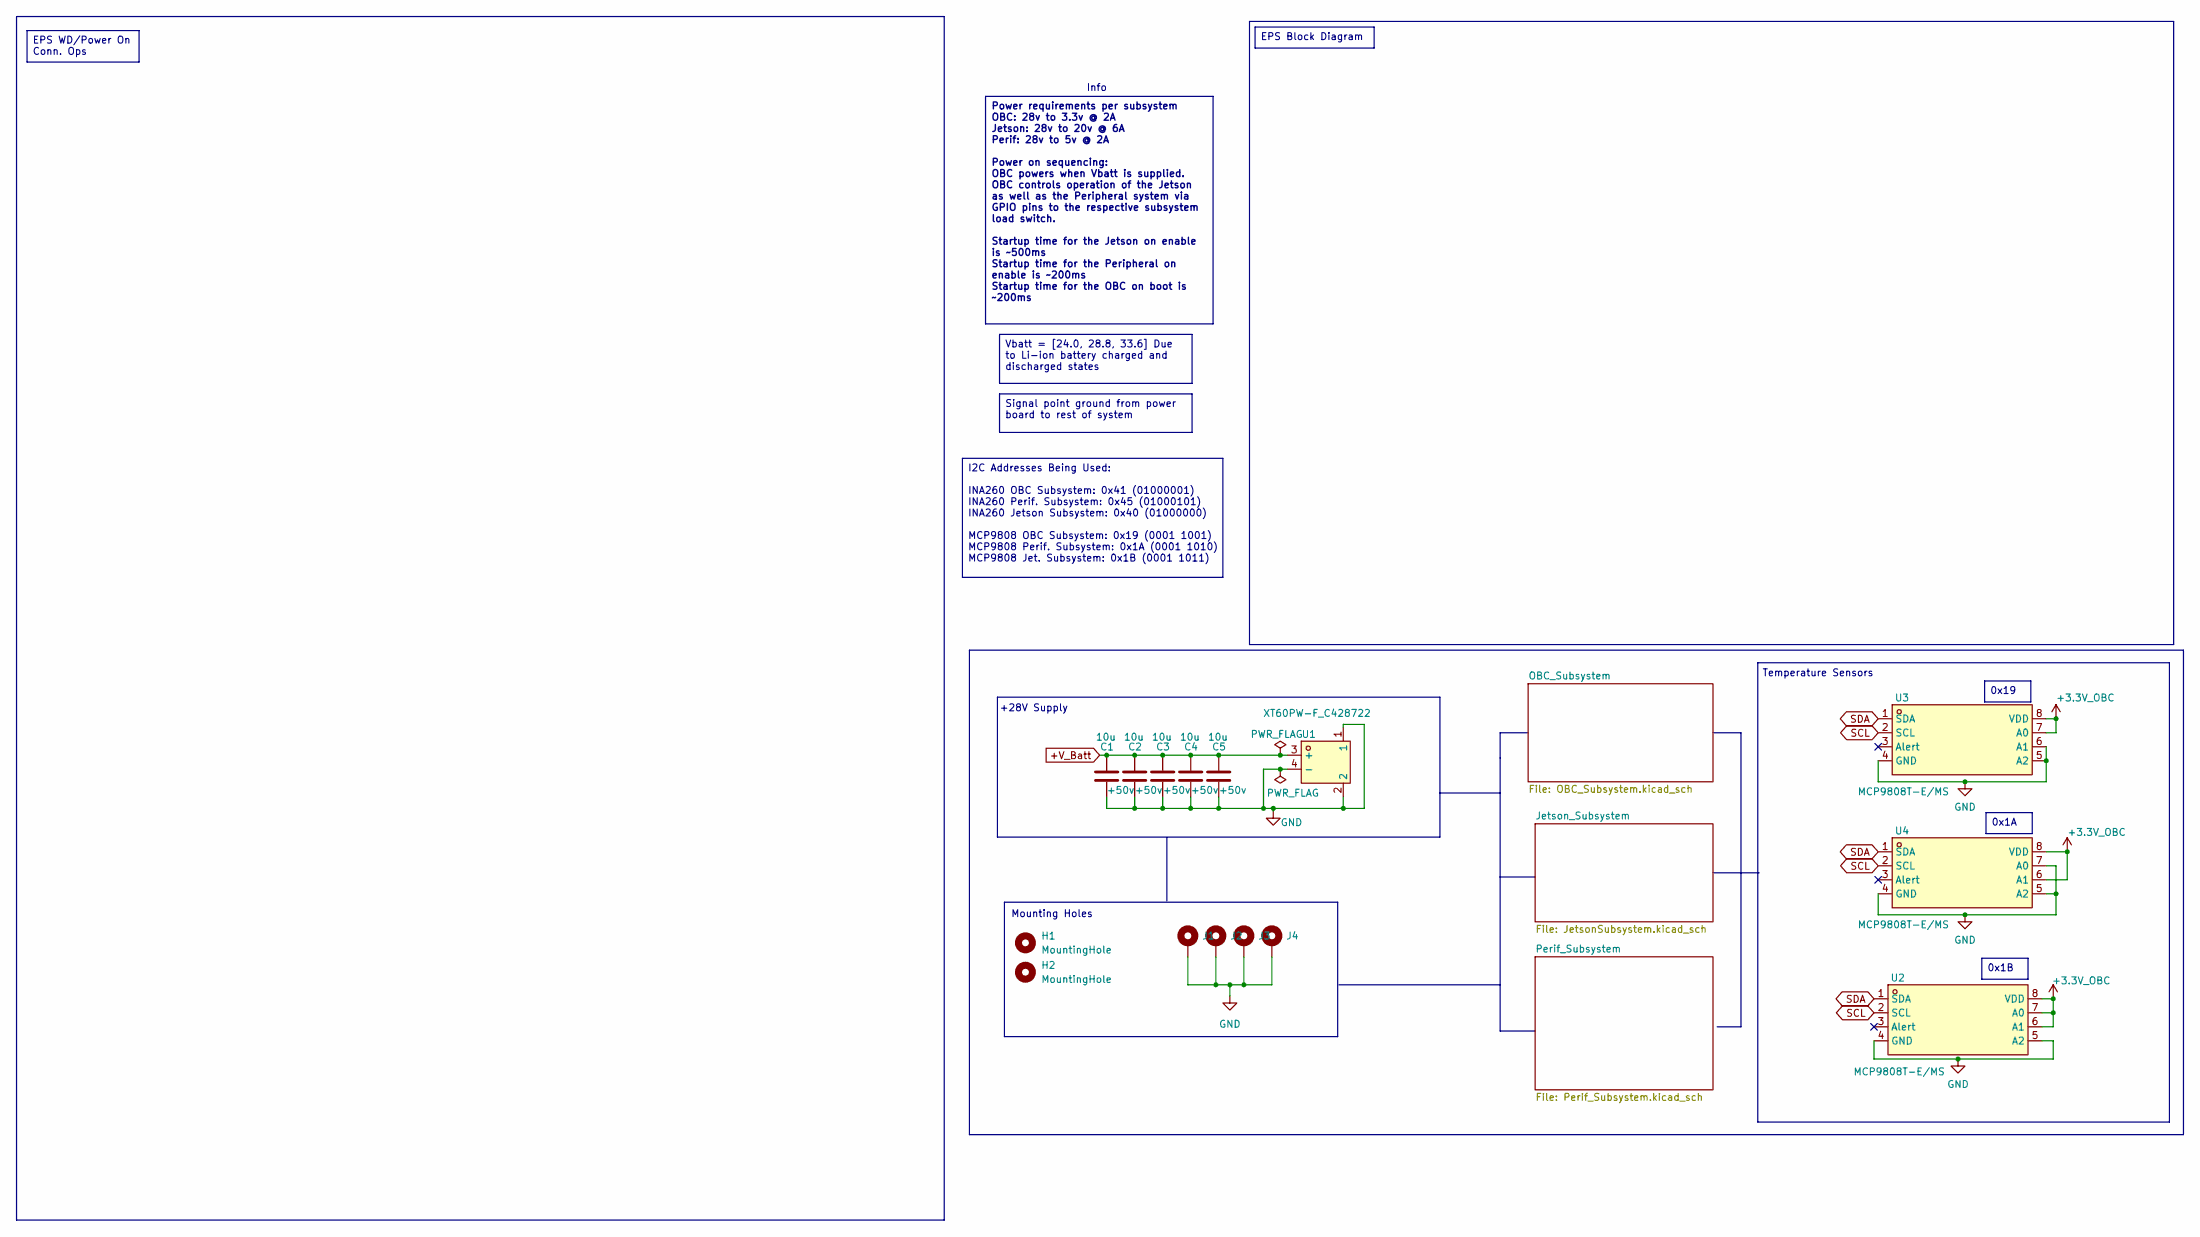
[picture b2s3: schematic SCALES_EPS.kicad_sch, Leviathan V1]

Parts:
C1, C2, C3, C4, C5: 10u; C_1210_3225Metric; Voltage Rating +50v; LCSC C2918502
H1, H2: MountingHole; MountingHole_2.7mm_M2.5
J1, J2, J3, J4: Conn_01x01_Socket; MountingHole_2.7mm_M2.5_DIN965_Pad
U1: XT60PW-F_C428722; TH_2P-XT60PW-F; LCSC Part C428722
U2, U3, U4: MCP9808T-E/MS; MSOP-8_L3.0-W3.0-P0.65-LS4.9-BL; LCSC Part C129490

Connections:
+3.3V_OBC: U2.6 (A1), U2.7 (A0), U2.8 (VDD), U3.7 (A0), U3.8 (VDD), U4.6 (A1), U4.8 (VDD); also elsewhere on the board
+V_Batt: C1.1, C2.1, C3.1, C4.1, C5.1, U1.3 (+); also elsewhere on the board
GND: C1.2, C2.2, C3.2, C4.2, C5.2, J1.1, J2.1, J3.1, J4.1, U1.1, U1.2, U1.4 (-), U2.4 (GND), U2.5 (A2), U3.4 (GND), U3.5 (A2), U3.6 (A1), U4.4 (GND), U4.5 (A2), U4.7 (A0); also elsewhere on the board
SCL: U2.2 (SCL), U3.2 (SCL), U4.2 (SCL); also elsewhere on the board
SDA: U2.1 (SDA), U3.1 (SDA), U4.1 (SDA); also elsewhere on the board

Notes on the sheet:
Temperature Sensors
Mounting Holes
+28V Supply
Info
0x19
Power requirements per subsystem OBC: 28v to 3.3v @ 2A Jetson: 28v to 20v @ 6A Perif: 28v to 5v @ 2A Power on sequencing: OBC powers when Vbatt is supplied. OBC controls operation of the Jetson as well as the Peripheral system via GPIO pins to the respective subsystem load switch. Startup time for 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
Signal point ground from power board to rest of system
Vbatt = [24.0, 28.8, 33.6] Due to Li-ion battery charged and discharged states
I2C Addresses Being Used: INA260 OBC Subsystem: 0x41 (01000001) INA260 Perif. Subsystem: 0x45 (01000101) INA260 Jetson Subsystem: 0x40 (01000000) MCP9808 OBC Subsystem: 0x19 (0001 1001) MCP9808 Perif. Subsystem: 0x1A (0001 1010) MCP9808 Jet. Subsystem: 0x1B (0001 1011)
EPS Block Diagram
0x1B
EPS WD/Power On Conn. Ops
0x1A
